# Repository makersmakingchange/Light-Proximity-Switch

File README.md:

# Light Proximity Switch

> [!IMPORTANT]
2026-Jan-16 Several of the electronic components in this design are no longer available. We are working to determine suitable replacements.

The Light Proximity Switch is an open-source assistive switch that is activated by movement or extremely light contact. It can be activated by waving a hand or limb over the device. This switch has an output cable with a standard 3.5 mm plug and it can be used to control a variety of switch-adapted devices including phones, computers, adapted toys, and gaming consoles.

The Light Proximity Switch is comprised of off-the-shelf electronics, a custom printed circuit board (PCB), and 3D printed parts.

The Light Proximity Switch is open assistive technology (OpenAT). Under the terms of the open source licenses, the device may be built, used, and improved by anyone.

The overall cost of materials for a single build is approximately $35 CAD.

## More info at

- [Makers Making Change Library Page](https://www.makersmakingchange.com/s/product/light-proximity-switch/01tJR0000006942YAA)

## Usage
Plug the 3.5 mm cable from the switch into the device you want to control. Wave a hand or limb over the sensor to trigger the device (the green LED should light up). 

Fine tune the motion sensitivity by toggling the black switch to "HI" or "LO" then fine tuning using the blue dial.

To attach the 3D printed circular base, simply slide the base onto the switch until it clicks into place. This may take a bit of force. The inclined surface of the can make it easier for a user to push their hand up to activate the sensor.

## How to Obtain the Device
### 1. Do-it-Yourself (DIY) or Do-it-Together (DIT)

This is an open-source assistive technology, so anyone is free to build it. All of the files and instructions required to build the device are contained within this repository. Refer to the documentation below.

### 2. Request a build of this device

You may also submit a build request through the [MMC Library Page](https://www.makersmakingchange.com/s/product/light-proximity-switch/01tJR0000006942YAA) to have a volunteer maker build the device. As the requestor, you are responsible for reimbursing the maker for the cost of materials and any shipping.

### 3. Build this device for someone else

If you have the skills and equipment to build this device, and would like to donate your time to create the device for someone who needs it, visit the [MMC Maker Wanted](https://makersmakingchange.com/maker-wanted/) section.

## Build Instructions

### 1. Read through the Documentation

<!--- The [Assembly Guide](/Documentation/Light_Proxity_Switch_Makery_Guide.pdf) contains all the necessary information to build this device, including tool lists, assembly instructions, and testing. --->
Read through the documentation below.

### 2. Order the Custom Printed Circuit Board (PCB)

This device requires a custom PCB. It will need to be ordered from a PCB fabrication service. The Gerber files can be found in the [PCB Build Files](/Build_Files/PCB_Build_Files/). 

### 3. Order the Off-The-Shelf Components

The [Bill of Materials](/Documentation/Light_Proximity_Switch_BOM.csv) lists all of the parts and components required to build the device. This build also requires a custom PCB.

### 4. Print the 3D Printable components

All of the individual print files can be found in the [/Build_Files/3D_Printing_Files](/Build_Files/3D_Printing_Files/) folder.

### 5. Assemble the Light Proximity Switch

Reference the [Assembly Guide](/Documentation/Light_Proxity_Switch_Assembly_Guide.pdf) for the tools and steps required to build each portion.

## How to improve this Device Design
As open assistive technology, you are welcomed and encouraged to improve upon the design. 

## Files
### Documentation
| Document             | Version | Link |
|----------------------|---------|------|
| Design Rationale     | n/a     | WIP   |
| Bill of Materials    | 1.0     |  [Light Proximity Switch BOM](/Documentation/Light_Proximity_Switch_BOM.csv)  |
| Tool List | 1.0 | [Light Proximity Switch Tools List](/Documentation/Light_Proximity_Switch_Tools_List.pdf)|
| Assembly Guide       | 1.0     | [Light Proximity Switch Assembly Guide](/Documentation/Light_Proxity_Switch_Assembly_Guide.pdf) |
| QC Quide | 1.0 | [Light Proximity Switch QC Guide](/Documentation/Light_Proximity_Switch_QC_Guide.pdf)|
| Troubleshooting Guide | 1.0 | [Light Proximity Switch Troubleshooting Guide](/Documentation/Light_Proximity_Switch_Troubleshooting_Guide.pdf)|
| Delivery Checklist | 1.0 | [Light Proximity Delivery Checklist](/Documentation/Light_Proximity_Switch_Delivery_Checklist.pdf)|
| User Guide           | 1.0     | [Light Proximity Switch User Guide](/Documentation/Light_Proximity_Switch_User_Guide.pdf) |
| Changelog            | n/a     | -     |

### Design Files
<!---
DESIGN FILES
--->
 - [CAD Files](/Design_Files/CAD_Design_Files)
 - [PCB Design Files](/Design_Files/PCB_Design_Files/)

### Build Files
 - [3D Printing Files](/Build_Files/3D_Printing_Files)
 - [PCB Build Files](/Build_Files/PCB_Build_Files)

## License
Copyright (c) 2019-2026 Neil Squire / Makers Making Change.

This repository describes Open Hardware:
 - Everything needed or used to design, make, test, or prepare the Light Proximity Switch is licensed under the [CERN 2.0 Weakly Reciprocal license (CERN-OHL-W v2) or later](https://cern.ch/cern-ohl ) .
 - Accompanying material such as instruction manuals, videos, and other copyrightable works that are useful but not necessary to design, make, test, or prepare the Light Proximity Switch are published under a [Creative Commons Attribution-ShareAlike 4.0 license (CC BY-SA 4.0)](https://creativecommons.org/licenses/by-sa/4.0/) .

You may redistribute and modify this documentation and make products using it under the terms of the [CERN-OHL-W v2](https://cern.ch/cern-ohl).
This documentation is distributed WITHOUT ANY EXPRESS OR IMPLIED WARRANTY, INCLUDING OF MERCHANTABILITY, SATISFACTORY QUALITY AND FITNESS FOR A PARTICULAR PURPOSE.
Please see the CERN-OHL-W v2 for applicable conditions.

Source Location: https://github.com/makersmakingchange/Light-Proximity-Switch

## Attribution
The Light Proximity Switch is an original design by Neil Squire / Maker Making Change Program.

### Contributors
  - Derrick Andrews, Neil Squire Society / Makers Making Change.
  - Jake McIvor, Neil Squire Society / Makers Making Change.
  - Kristina Mok, Neil Squire Society / Makers Making Change.

<!-- ABOUT MMC START -->
## About Makers Making Change

Makers Making Change is a program of [Neil Squire](https://www.neilsquire.ca/), a Canadian non-profit that uses technology, knowledge, and passion to empower people with disabilities.

Makers Making Change leverages the capacity of community based Makers, Disability Professionals and Volunteers to develop and deliver affordable Open Source Assistive Technologies.

 - Website: [www.MakersMakingChange.com](https://www.makersmakingchange.com/)
 - GitHub: [makersmakingchange](https://github.com/makersmakingchange)
 - Bluesky: [@makersmakingchange.bsky.social](https://bsky.app/profile/makersmakingchange.bsky.social)
 - Instagram: [@makersmakingchange](https://www.instagram.com/makersmakingchange)
 - Facebook: [makersmakechange](https://www.facebook.com/makersmakechange)
 - LinkedIn: [Neil Squire Society](https://www.linkedin.com/company/neil-squire-society/)
 - Thingiverse: [makersmakingchange](https://www.thingiverse.com/makersmakingchange/about)
 - Printables: [MakersMakingChange](https://www.printables.com/@MakersMakingChange)

### Contact Us
For technical questions, to get involved, or to share your experience we encourage you to [visit our website](https://www.makersmakingchange.com/) or [contact us](https://www.makersmakingchange.com/s/contact).
<!-- ABOUT MMC END -->

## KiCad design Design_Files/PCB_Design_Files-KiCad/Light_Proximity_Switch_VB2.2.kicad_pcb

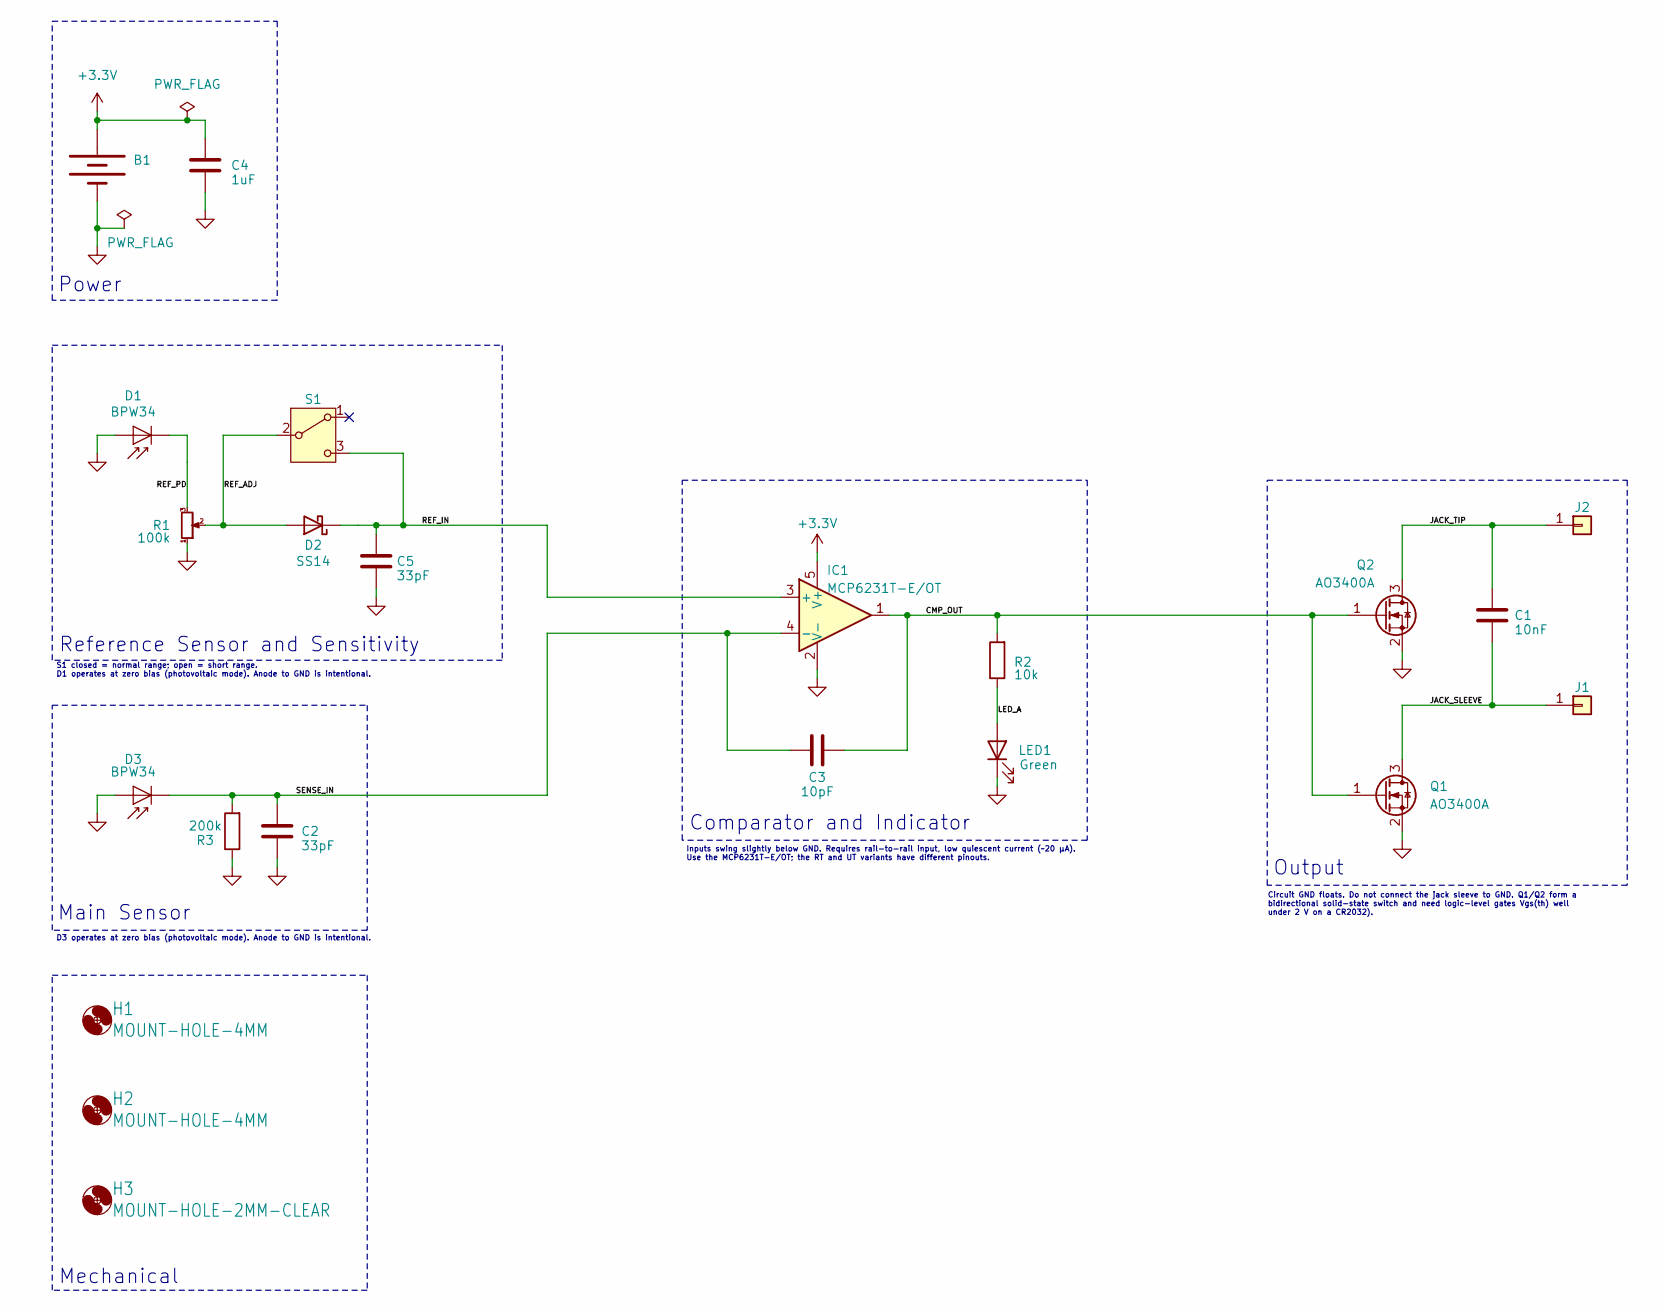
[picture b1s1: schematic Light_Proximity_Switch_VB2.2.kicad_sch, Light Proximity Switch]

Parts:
B1: CR2032_SMT_HOLDER
C1: 10nF; C_0805_2012Metric_Pad1.18x1.45mm_HandSolder; LCSC C1710
C2, C5: 33pF; C_0603_1608Metric_Pad1.08x0.95mm_HandSolder; LCSC C1663
C3: 10pF; C_0603_1608Metric_Pad1.08x0.95mm_HandSolder; LCSC C1634
C4: 1uF; C_0805_2012Metric_Pad1.18x1.45mm_HandSolder; LCSC C28323
D1, D3: BPW34; Osram_DIL2_4.3x4.65mm_P5.08mm
D2: SS14; D_SMA_Handsoldering; LCSC C2480
H1, H2: MOUNT-HOLE-4MM; HOLE-4MM
H3: MOUNT-HOLE-2MM-CLEAR; HOLE-2MM-CLEAR
IC1: MCP6231T-E/OT; SOT-23-5; LCSC C2894704
J1, J2: Conn_01x01; PAD-1X01
LED1: Green; LED_D5.0mm
Q1, Q2: AO3400A; SOT-23; LCSC C20917
R1: 100k; Potentiometer_Bourns_3386P_Vertical
R2: 10k; R_0805_2012Metric_Pad1.20x1.40mm_HandSolder; LCSC C17414
R3: 200k; R_0805_2012Metric_Pad1.20x1.40mm_HandSolder; LCSC C17539
S1: SWITCH_SPDT_PTH_11.6X4.0MM

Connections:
+3.3V: B1.+, C4.1, IC1.5 (V+)
/CMP_OUT: C3.2, IC1.1, Q1.1 (G), Q2.1 (G), R2.2
/JACK_SLEEVE: C1.2, J1.1 (Pin_1_1), Q1.3 (D)
/JACK_TIP: C1.1, J2.1 (Pin_1_1), Q2.3 (D)
/LED_A: LED1.2 (A), R2.1
/REF_ADJ: D2.2 (A), R1.2, S1.2 (B)
/REF_IN: C5.1, D2.1 (K), IC1.3 (+), S1.3 (C)
/REF_PD: D1.1 (K), R1.3
/SENSE_IN: C2.1, C3.1, D3.1 (K), IC1.4 (-), R3.2
GND: B1.-, C2.2, C4.2, C5.2, D1.2 (A), D3.2 (A), IC1.2 (V-), LED1.1 (K), Q1.2 (S), Q2.2 (S), R1.1, R3.1

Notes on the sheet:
Output
Comparator and Indicator
Power
S1 closed = normal range; open = short range. D1 operates at zero bias (photovoltaic mode). Anode to GND is intentional.
Main Sensor
Circuit GND floats. Do not connect the jack sleeve to GND. Q1/Q2 form a bidirectional solid-state switch and need logic-level gates Vgs(th) well under 2 V on a CR2032).
D3 operates at zero bias (photovoltaic mode). Anode to GND is intentional.
Mechanical
Reference Sensor and Sensitivity
Inputs swing slightly below GND. Requires rail-to-rail input, low quiescent current (~20 µA). Use the MCP6231T-E/OT; the RT and UT variants have different pinouts.

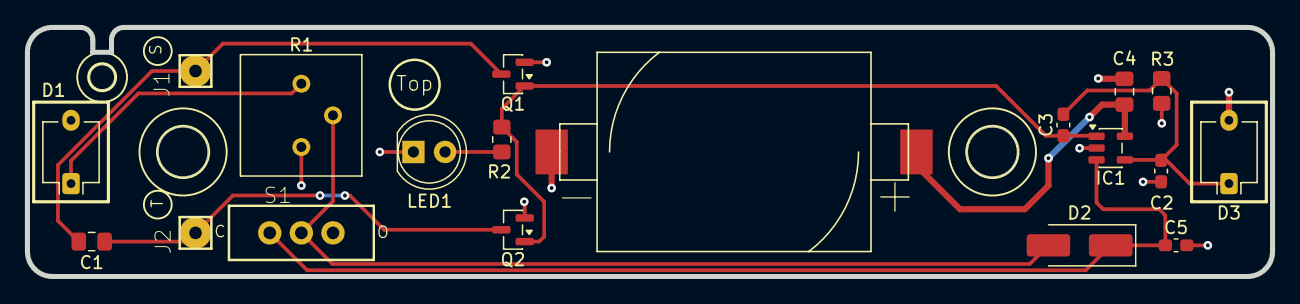
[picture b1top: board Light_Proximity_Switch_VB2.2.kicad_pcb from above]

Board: 2 copper layers, 100.0 x 20.0 mm, 22 parts (0 on the bottom side), 10 nets.

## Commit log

2020-05-06 Update Light_Proximity_Switch_Base_v1.0.stl
    Correct default orientation.
2020-05-06 Update 3D Print info
    Add 3d printing settings and orientation photo
2020-05-07 Correct folder naming
2020-05-07 Correct folder naming Pt 2
2020-05-08 Added the PCB Fabrication Manual
2020-05-13 Added gerber files and board/schematics pdf files.
2020-05-13 Added MMC PCB Fabrication Manual document.
2020-09-16 Update Forum link
2021-04-01 Added PCBWay gerbers
2021-07-02 Create Light_Proximity_Switch_BOM_v1.0.md
    Add markdown version of BOM
2021-07-02 Add Assembly Guide version
2021-07-02 Delete Light_Proximity_Switch_Delivery_Checklist.pdf
    Remove duplicate
2021-07-02 Standardize User Guide filename
2025-04-04 Update to bottom case and renaming
    - Updated the bottom case model so improve printing of the unsupported screw holes.
    - Renamed stl files to remove versioning to make consistent with newer libraries
    - Added .STEP files in Design_Files folder
2025-04-08 Update About MMC Section
2025-04-10 Add Update About MMC GitHub Action
2026-01-17 Update and expand license documentation
2026-01-17 Add images for light proximity switch project
    Added three new image files: Light_Proximity_Usage.gif, Light_Proximity_Switch.jpg, and Light_Proximity_switch_Base.gif to the Photos directory
2026-01-17 Rename and reorganize documentation
2026-01-17 Rename 3D printing file folder to match OpenAT Template
    3D_Printing -> 3D_Printing_Files
2026-01-17 Reorganize PCB files
2026-01-17 Reogranize CAD files
2026-01-17 Update Light Proximity Switch BOM components and pricing
    Revised the Bill of Materials for the Light Proximity Switch to update suppliers, manufacturers, part numbers, and pricing. Notable changes include switching the op-amp to MCP6231-E/P, updating sever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
2026-04-08 Updated Base File
    Added the correct base file as the previous one was a accidental copy of the bottom case. This is relevant to Issue: ""Base" file is wrong #11"
